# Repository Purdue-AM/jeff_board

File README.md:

# jeff_boardV2
A straightforward Arduino Nano breakout board that allows for driving 2 PWM lines up to 30V, powered on 12/24V, and connects to two thermal sensors. 

V2 is a revision of the original jeff Board to have 4 total 24V PWM lines, which will allow controlling UV LEDs, another heater, or another fan. There's plenty of space to add a step-down to 12V if one already has 12V UV LEDs.

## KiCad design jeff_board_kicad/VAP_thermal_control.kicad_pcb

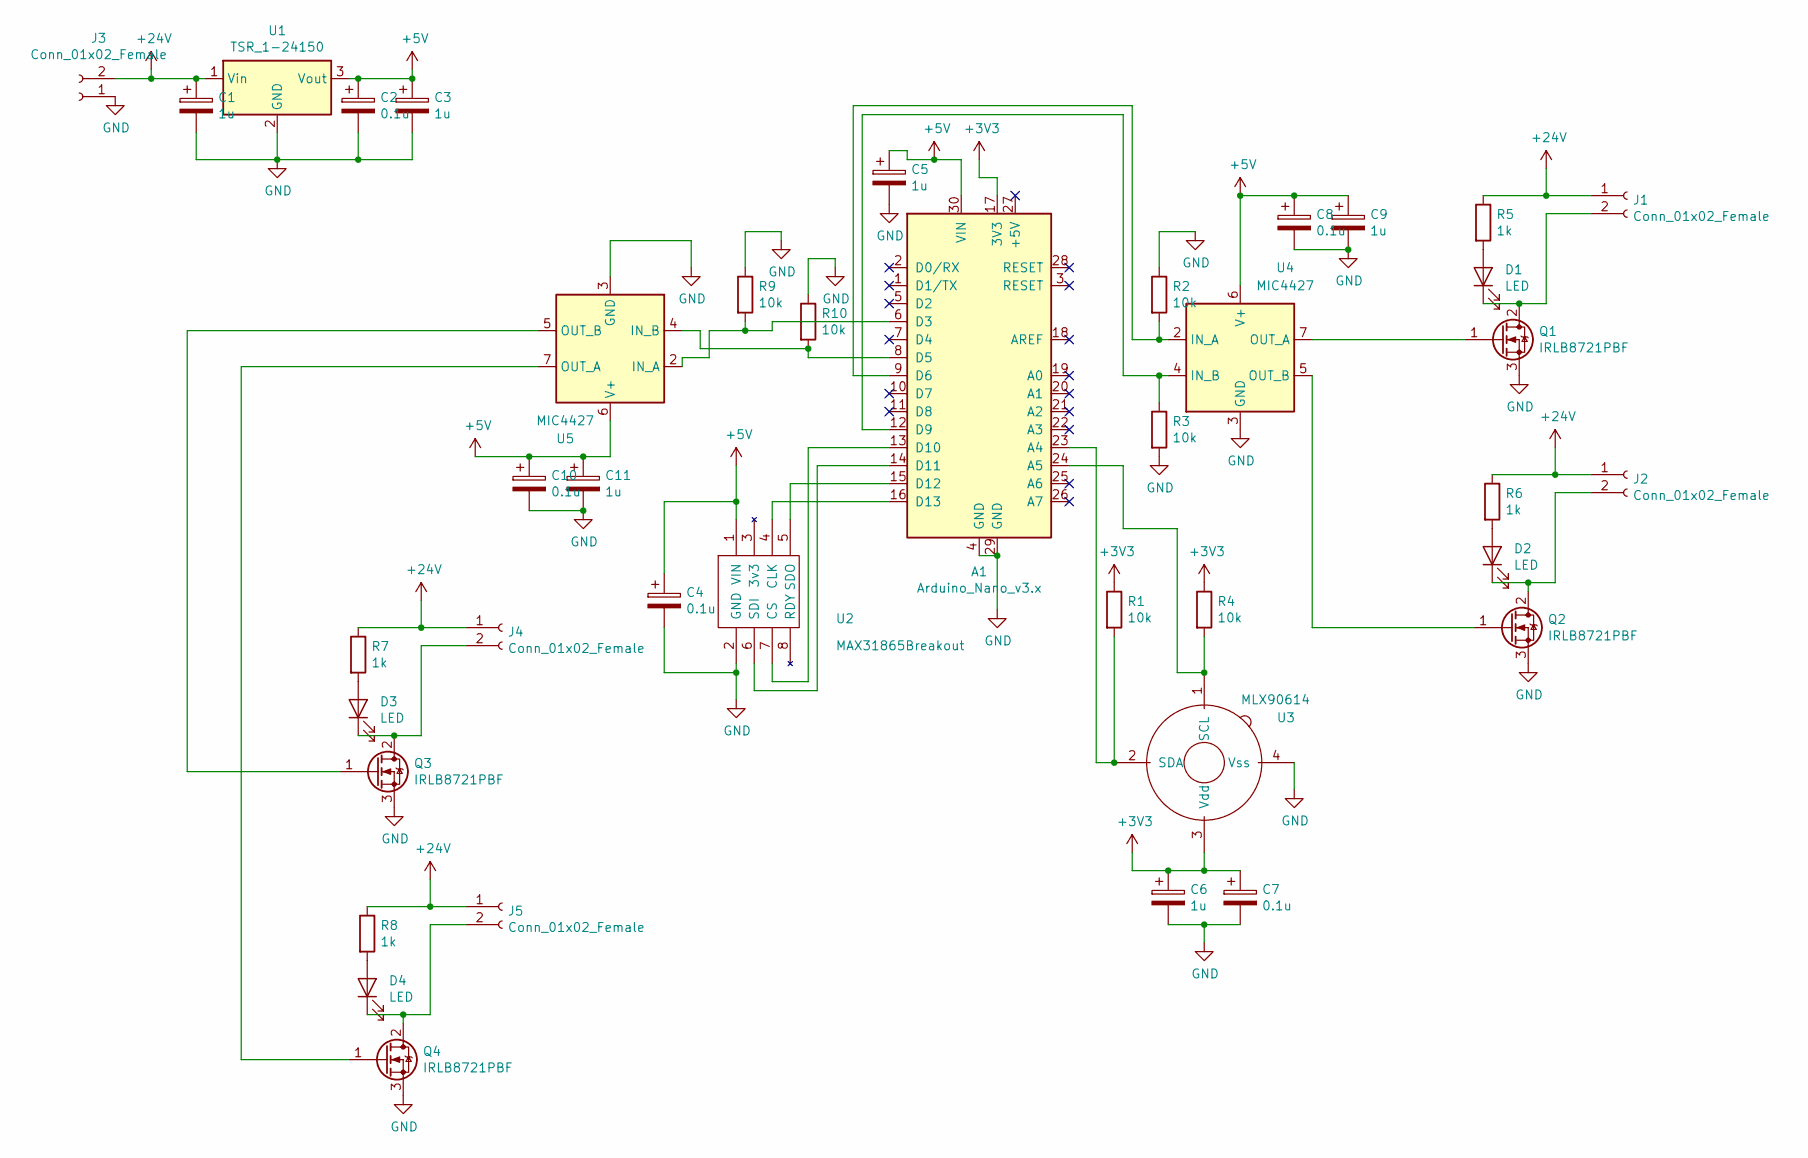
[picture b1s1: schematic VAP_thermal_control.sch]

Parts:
A1: Arduino_Nano_v3.x; Arduino_Nano
C1, C3, C5, C6, C9, C11: 1u; CP_Radial_D5.0mm_P2.00mm
C2, C4, C7, C8, C10: 0.1u; CP_Radial_D5.0mm_P2.00mm
D1, D2, D3, D4: LED; LED_D5.0mm
J1, J2, J3, J4, J5: Conn_01x02_Female; PhoenixContact_MSTBVA-G_02x5.00mm_Vertical
Q1, Q2, Q3, Q4: IRLB8721PBF; TO-220-3_Vertical
R1, R2, R3, R4, R9, R10: 10k; R_0805_HandSoldering
R5, R6, R7, R8: 1k; R_0805_HandSoldering
U1: TSR_1-24150; TO-220-3_Vertical
U2: MAX31865Breakout; Pin_Header_Straight_1x08_Pitch2.54mm
U3: MLX90614; TO-39-4_Window
U4, U5: MIC4427; DIP-8_W7.62mm

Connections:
+3V3: A1.17 (3V3), C6.1, C7.1, R1.1, R4.1, U3.3 (Vdd)
+5V: A1.30 (VIN), C2.1, C3.1, C4.1, C5.1, C8.1, C9.1, C10.1, C11.1, U1.3 (Vout), U2.1 (VIN), U4.6 (V+), U5.6 (V+)
+24V: C1.1, J1.1, J2.1, J3.2, J4.1, J5.1, R5.1, R6.1, R7.1, R8.1, U1.1 (Vin)
GND: A1.4 (GND), A1.29 (GND), C1.2, C2.2, C3.2, C4.2, C5.2, C6.2, C7.2, C8.2, C9.2, C10.2, C11.2, J3.1, Q1.3 (S), Q2.3 (S), Q3.3 (S), Q4.3 (S), R2.1, R3.2, R9.1, R10.1, U1.2 (GND), U2.2 (GND), U3.4 (Vss), U4.3 (GND), U5.3 (GND)
unnamed: A1.6 (D3), R9.2, U5.2 (IN_A)
unnamed: A1.8 (D5), R10.2, U5.4 (IN_B)
unnamed: A1.9 (D6), R2.2, U4.2 (IN_A)
unnamed: A1.12 (D9), R3.1, U4.4 (IN_B)
unnamed: A1.13 (D10), U2.7 (CS)
unnamed: A1.14 (D11), U2.6 (SDI)
unnamed: A1.15 (D12), U2.5 (SDO)
unnamed: A1.16 (D13), U2.4 (CLK)
unnamed: A1.23 (A4), R1.2, U3.2 (SDA)
unnamed: A1.24 (A5), R4.2, U3.1 (SCL)
unnamed: D1.1 (K), J1.2, Q1.2 (D)
unnamed: D1.2 (A), R5.2
unnamed: D2.1 (K), J2.2, Q2.2 (D)
unnamed: D2.2 (A), R6.2
unnamed: D3.1 (K), J4.2, Q3.2 (D)
unnamed: D3.2 (A), R7.2
unnamed: D4.1 (K), J5.2, Q4.2 (D)
unnamed: D4.2 (A), R8.2
unnamed: Q1.1 (G), U4.7 (OUT_A)
unnamed: Q2.1 (G), U4.5 (OUT_B)
unnamed: Q3.1 (G), U5.5 (OUT_B)
unnamed: Q4.1 (G), U5.7 (OUT_A)

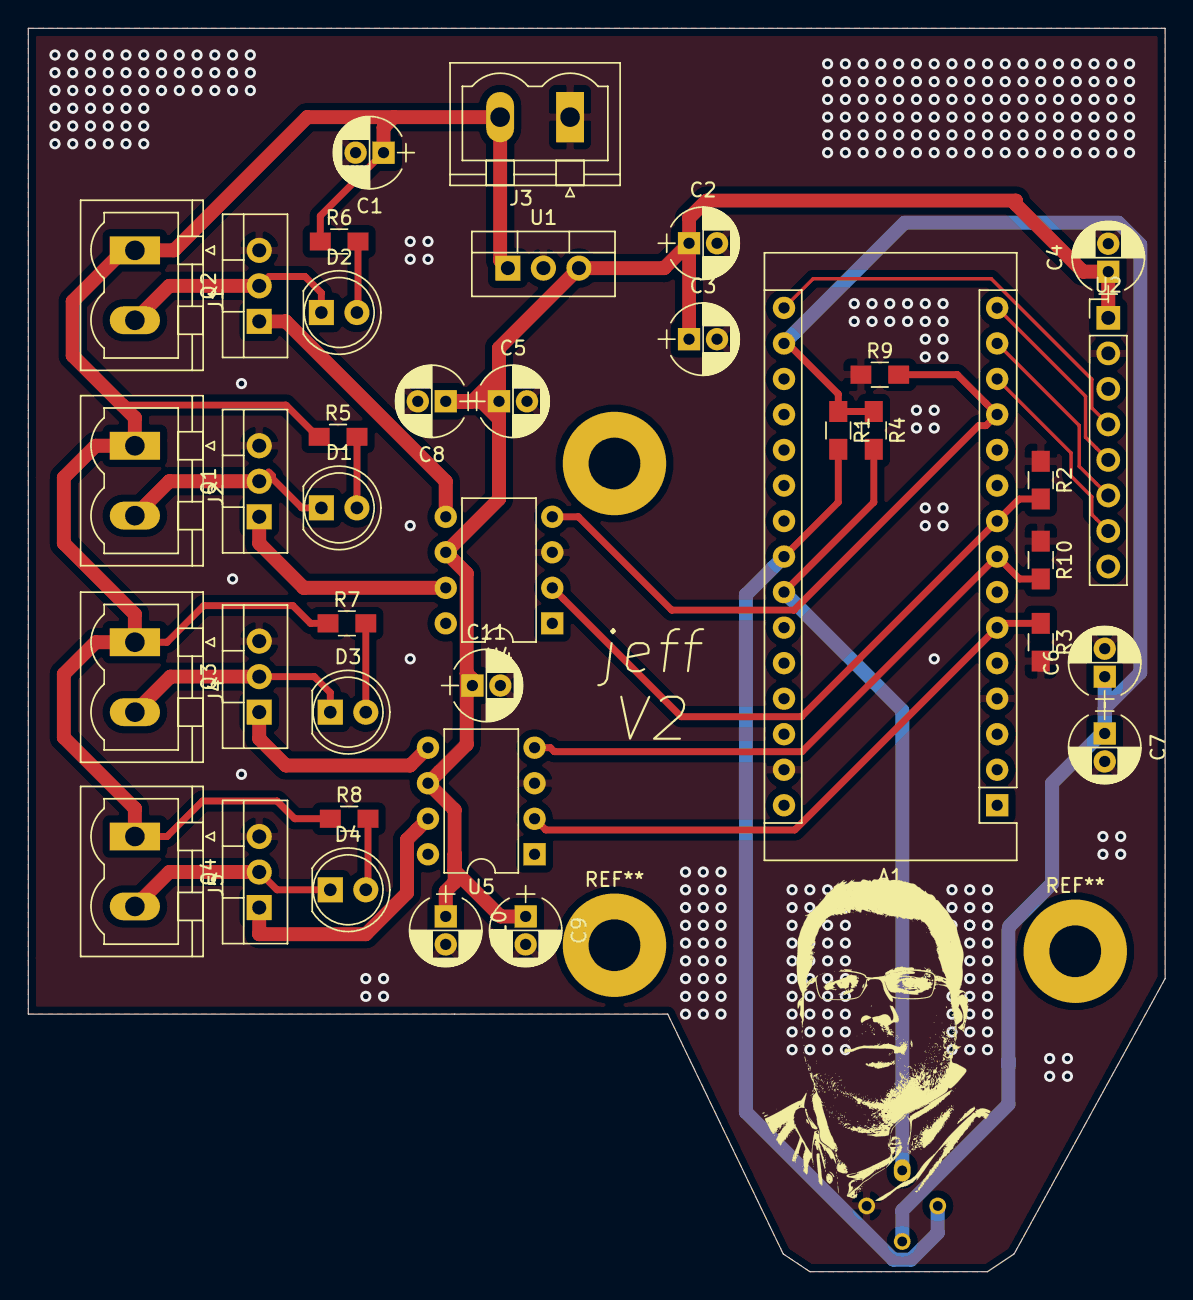
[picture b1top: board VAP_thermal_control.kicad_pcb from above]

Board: 2 copper layers, 81.3 x 88.9 mm, 40 parts (1 on the bottom side), 26 nets.

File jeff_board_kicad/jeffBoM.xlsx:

Source: | C:\Users\JC\Documents\GitHub\jeff_board\jeff_board_kicad\VAP_thermal_control.sch
Date: | 43730.320486111108
Tool: | Eeschema (5.1.2)-1
Generator: | C:\Program Files\KiCad\bin\scripting\plugins/bom_csv_grouped_by_value_with_fp.py
Component Count: | 40
Ref | Qnty | Value | Cmp name | Footprint | Description | Vendor | Digikey Part # | Adafruit Part # | Cost (from Digikey) | Total Items Cost
A1, | 1 | Arduino_Nano_v3.x | Arduino_Nano_v3.x | Modules:Arduino_Nano | Arduino Nano v3.x | Digikey|Adafruit |  |  | 22 | 22
C2, C4, C7, C8, C10, | 5 | 0.1u | CP | Capacitors_THT:CP_Radial_D5.0mm_P2.00mm | Polarized capacitor | Digikey |  |  | 0.1 | 0.5
C3, C1, C5, C6, C9, C11, | 6 | 1u | CP | Capacitors_THT:CP_Radial_D5.0mm_P2.00mm | Polarized capacitor | Digikey |  |  | 0.23 | 1.3800000000000001
D1, D2, D3, D4, | 4 | LED | LED | LEDs:LED_D5.0mm | Light emitting diode | Digikey|Adafruit |  |  | 0.2 | 0.8
J1, J2, J3, J4, J5, | 5 | Conn_01x02_Female | Conn_01x02_Female | Connectors_Phoenix:PhoenixContact_MSTBVA-G_02x5.00mm_Vertical | Pheonix screw terminal, single row, 01x02 | Digikey |  |  | 0.48 | 2.4
Q1, Q2, Q3, Q4, | 4 | IRLB8721PBF | IRLB8721PBF | TO_SOT_Packages_THT:TO-220-3_Vertical | 62A Id, 30V Vds, N-Channel MOSFET, TO-220 | Digikey|Adafruit |  |  | 2.8 | 11.2
R1, R4, R2, R3, R9, R10, | 6 | 10k | R | Resistors_SMD:R_0805_HandSoldering | Resistor | Digikey, Sorta Adafruit |  |  | 0.1 | 0.60000000000000009
R5, R6, R7, R8, | 4 | 1k | R | Resistors_SMD:R_0805_HandSoldering | Resistor | Digikey, Sorta Adafruit |  |  | 0.1 | 0.4
U1, | 1 | TSR_1-24150 | TSR_1-24150 | TO_SOT_Packages_THT:TO-220-3_Vertical | 1A step-down regulator module, fixed 15V output voltage, 8-36V input voltage, -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 | Digikey|Adafruit |  |  | 6.14 | 6.14
RTD Sensor | 1 | PT100 | RTD Temp Sensor, 100 or 1000 ohm | N/A | 3 wire from adafruit, match resistance to the amplifier board. | Digikey|Adafruit |  |  | 11.95 | 11.95
U2, | 1 | MAX31865Breakout | MAX31865Breakout | Pin_Headers:Pin_Header_Straight_1x08_Pitch2.54mm |  | Digikey|Adafruit |  |  | 14.95 | 14.95
U3, | 1 | MLX90614 | MLX90614 | TO_SOT_Packages_THT:TO-39-4_Window | Infra Red Thermometer in TO-39 package. | Digikey|Adafruit |  |  | 14.55 | 14.55
U4, U5, | 2 | MIC4427 | MIC4427 | Housings_DIP:DIP-8_W7.62mm | Dual 1.5A-Peak Low-Side MOSFET Driver, DIP-8/SOIC-8/MSOP-8 | Digikey | 576-1205-ND |  | 1.33 | 2.66
PCB | 1 | ENIG (Gold Plated) | jeff | -- | Custom PCB from JLCPCB.com | JLCPCB (cost is approx w/ shipping |  |  | 30 | 30
Total Cost: |  |  |  |  |  |  |  |  |  | 119.53

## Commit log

2019-09-11 V0.1 Board Layout
    Based on the original VAP thermal controller, this is the V0.1 layout (corrected grounding fill error on the arduino pinout)
2019-09-16 Update README.md
    description of what components are on the board, what they do.
2019-09-21 Prelim Layout of jeff V2
    Added two channels of PWM, so we can drive 4 of (Fan/Heater/LEDs).
2019-09-22 BoM added for jeffV2
